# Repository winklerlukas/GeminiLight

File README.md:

GeminiLight
===========

Arduino Temperature MultiColour Project

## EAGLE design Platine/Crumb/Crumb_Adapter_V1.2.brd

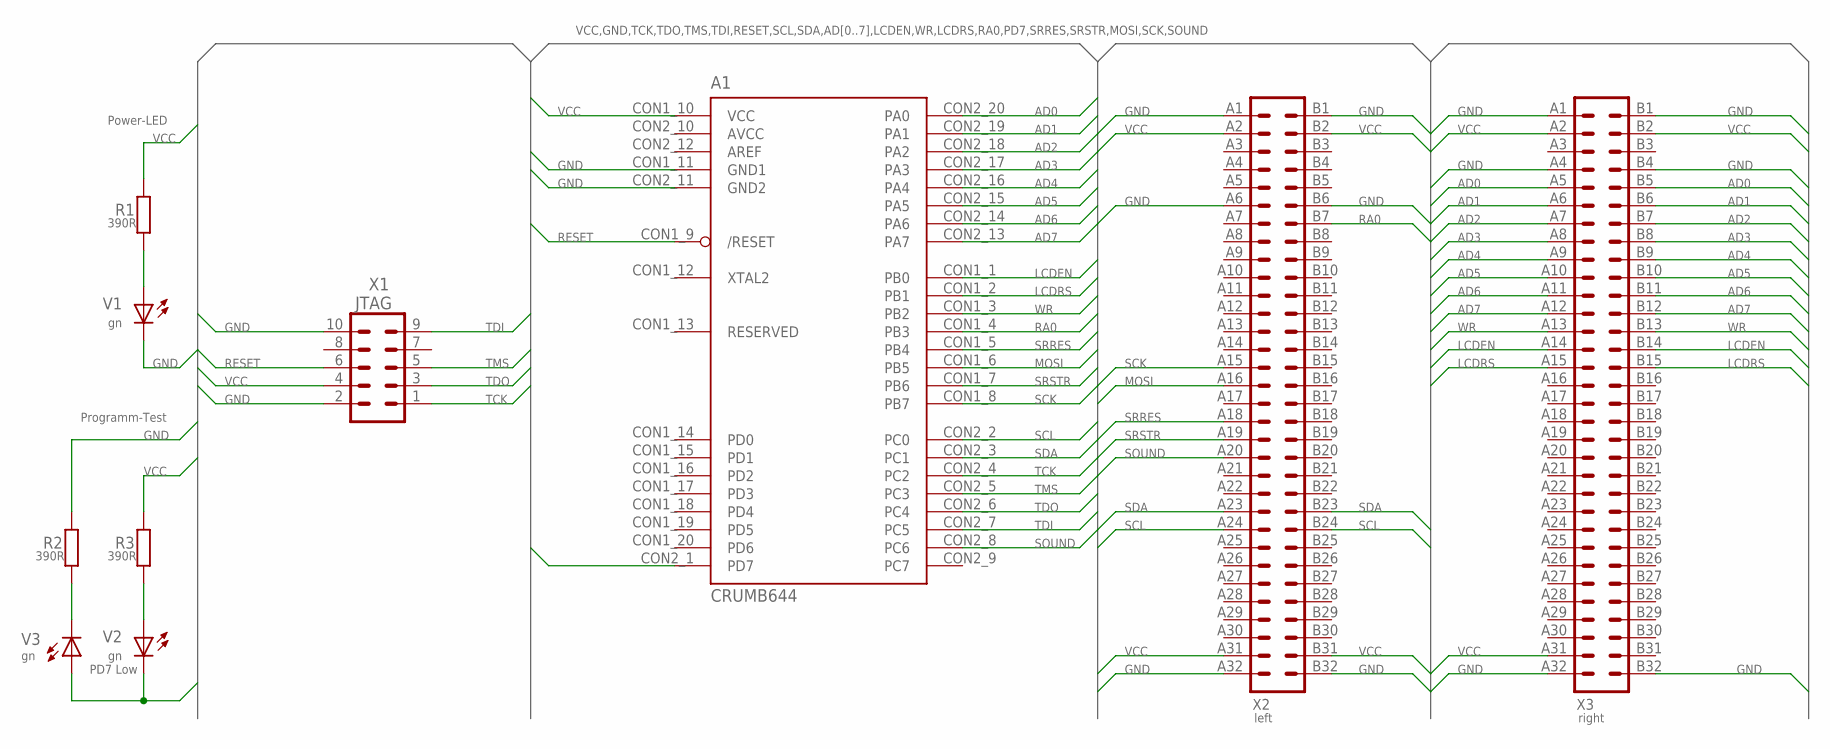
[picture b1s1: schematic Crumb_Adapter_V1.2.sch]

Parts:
A1: CRUMB644
R1, R2, R3: 390R; M1206
V1, V2, V3: gn; CHIPLED_1206
X1: JTAG; MA05-2
X2: left; MAB32-2
X3: right; MAB32-2

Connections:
AD0: A1.CON2_20 (PA0), X3.A5, X3.B5
AD1: A1.CON2_19 (PA1), X3.A6, X3.B6
AD2: A1.CON2_18 (PA2), X3.A7, X3.B7
AD3: A1.CON2_17 (PA3), X3.A8, X3.B8
AD4: A1.CON2_16 (PA4), X3.A9, X3.B9
AD5: A1.CON2_15 (PA5), X3.A10, X3.B10
AD6: A1.CON2_14 (PA6), X3.A11, X3.B11
AD7: A1.CON2_13 (PA7), X3.A12, X3.B12
GND: A1.CON1_11 (GND1), A1.CON2_11 (GND2), R2.2, V1.C, X1.2, X1.10, X2.A1, X2.A6, X2.A32, X2.B1, X2.B6, X2.B32, X3.A1, X3.A4, X3.A32, X3.B1, X3.B4, X3.B32
LCDEN: A1.CON1_1 (PB0), X3.A14, X3.B14
LCDRS: A1.CON1_2 (PB1), X3.A15, X3.B15
MOSI: A1.CON1_6 (PB5), X2.A16
unnamed: R1.1, V1.A
unnamed: R3.1, V2.A
unnamed: R2.1, V3.C
PD7: A1.CON2_1 (PD7), V2.C, V3.A
RA0: A1.CON1_4 (PB3), X2.B7
RESET: A1.CON1_9 (/RESET), X1.6
SCK: A1.CON1_8 (PB7), X2.A15
SCL: A1.CON2_2 (PC0), X2.A24, X2.B24
SDA: A1.CON2_3 (PC1), X2.A23, X2.B23
SOUND: A1.CON2_8 (PC6), X2.A20
SRRES: A1.CON1_5 (PB4), X2.A18
SRSTR: A1.CON1_7 (PB6), X2.A19
TCK: A1.CON2_4 (PC2), X1.1
TDI: A1.CON2_7 (PC5), X1.9
TDO: A1.CON2_6 (PC4), X1.3
TMS: A1.CON2_5 (PC3), X1.5
VCC: A1.CON1_10 (VCC), R1.2, R3.2, X1.4, X2.A2, X2.A31, X2.B2, X2.B31, X3.A2, X3.A31, X3.B2
WR: A1.CON1_3 (PB2), X3.A13, X3.B13

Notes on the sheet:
PD7 Low
Programm-Test
Power-LED

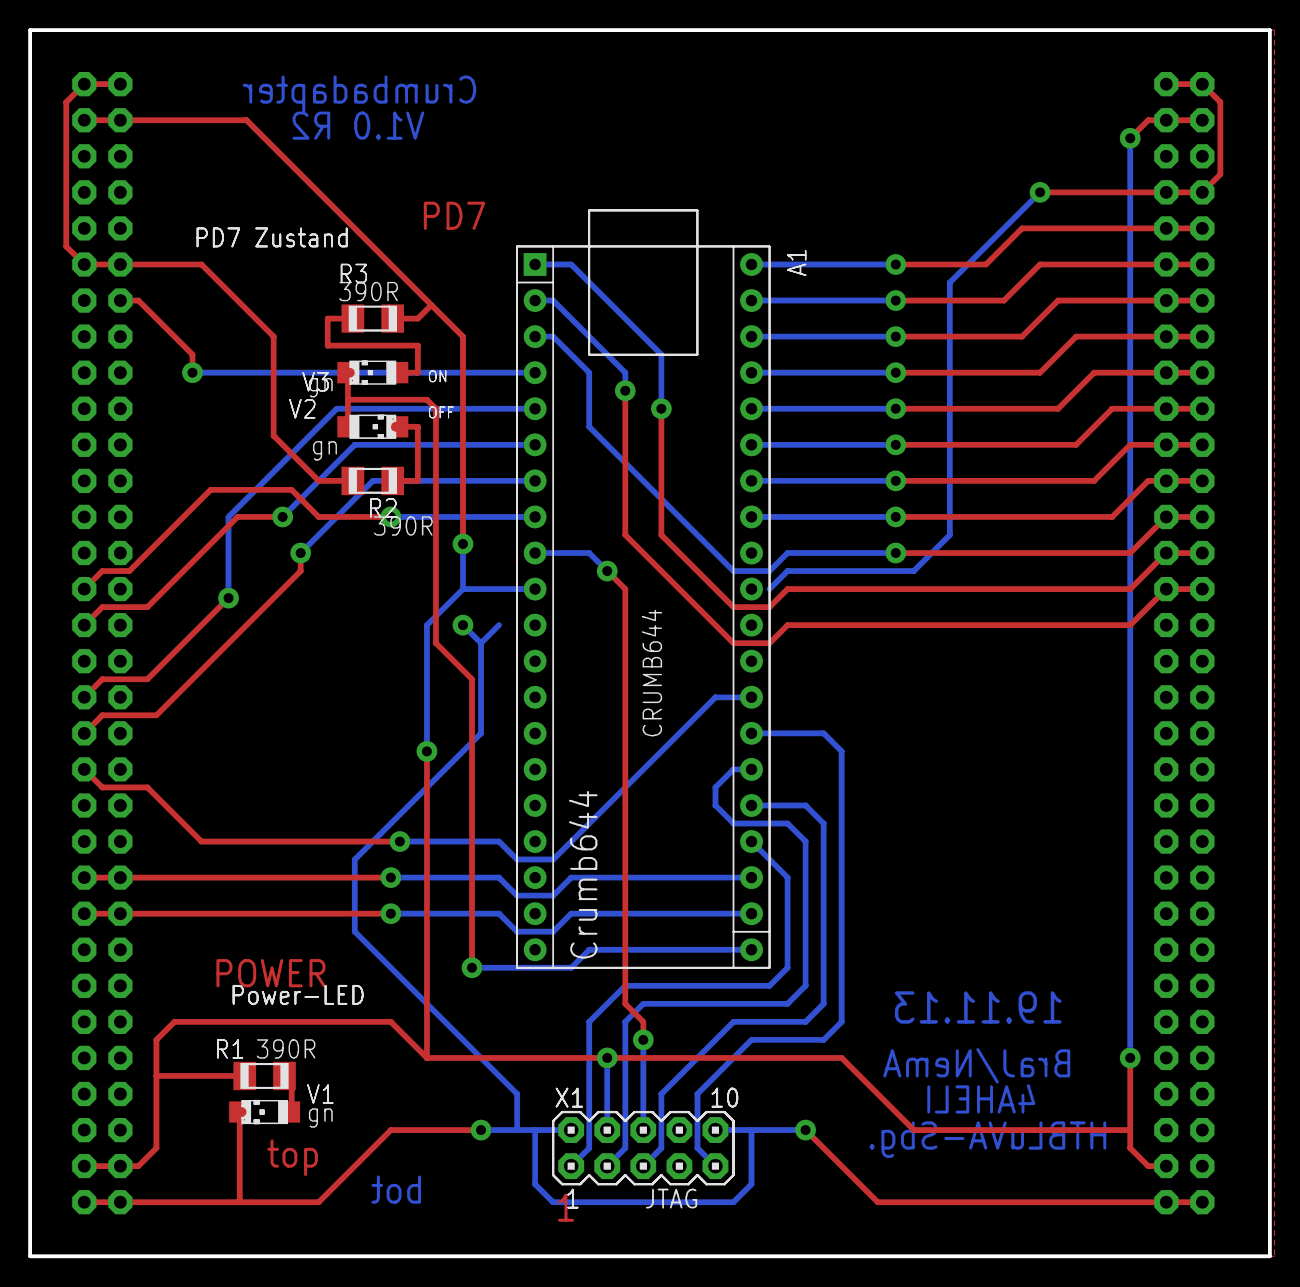
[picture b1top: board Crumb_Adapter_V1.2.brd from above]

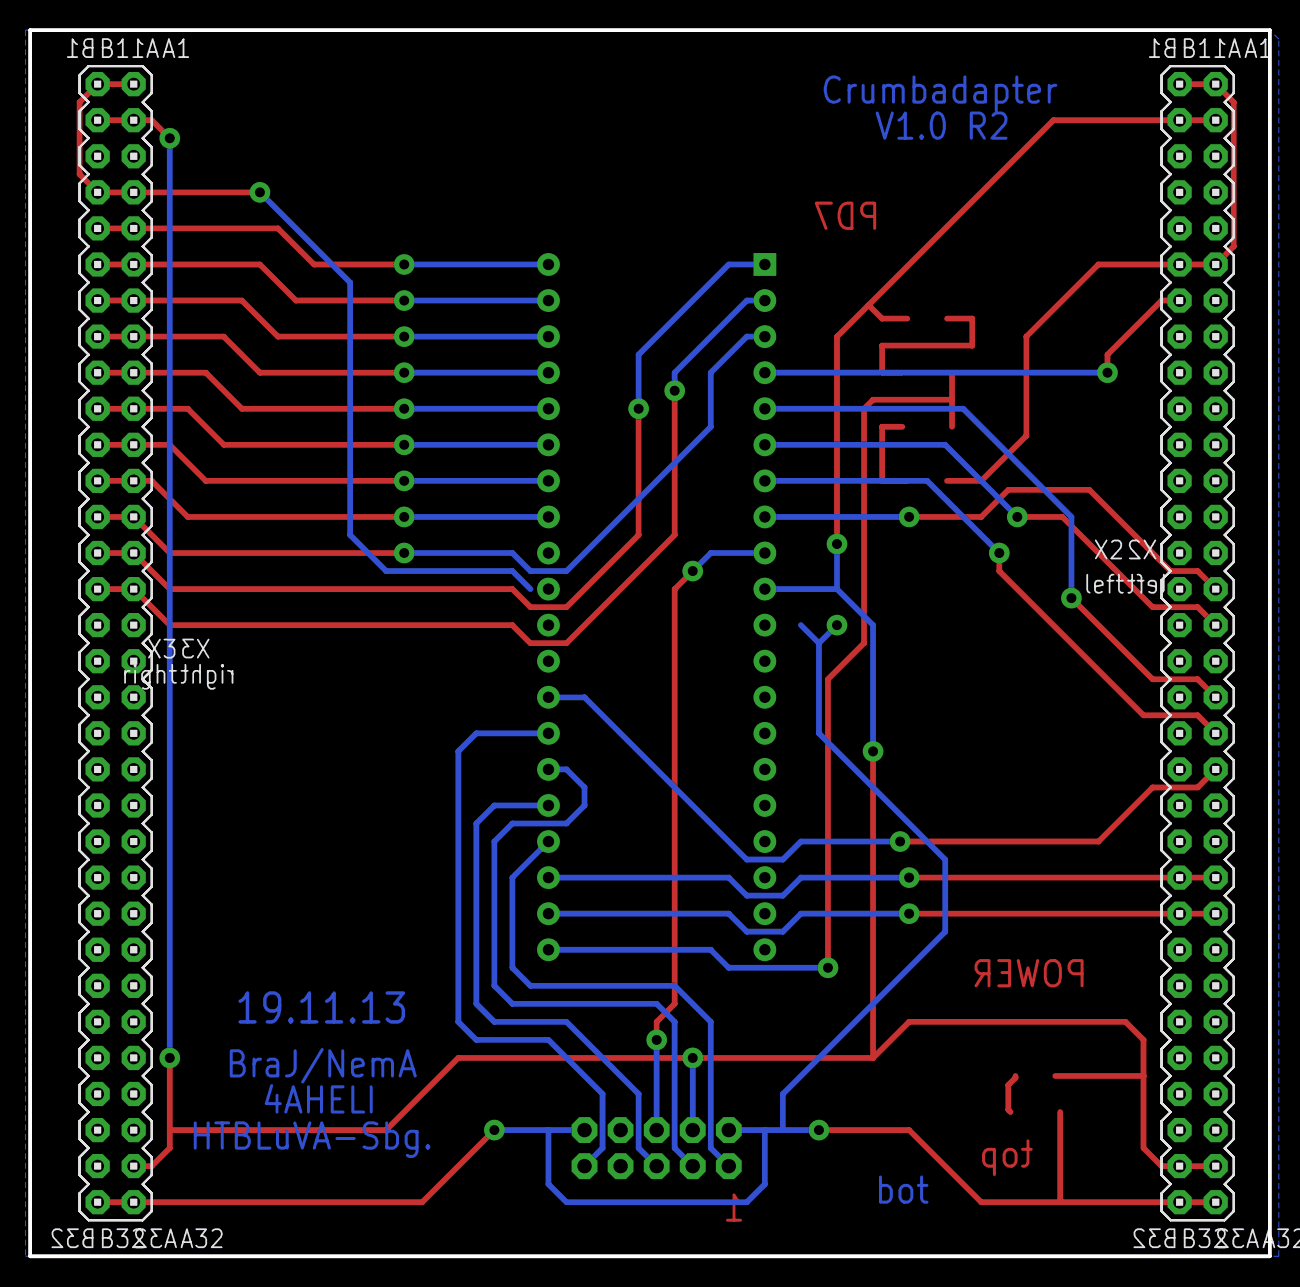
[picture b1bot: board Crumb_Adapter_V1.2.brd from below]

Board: 2 copper layers, 87.3 x 86.3 mm, 12 parts (2 on the bottom side), 30 nets.

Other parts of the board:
DRILEGEND: DRILEGEND
MEASURE: MEASURE

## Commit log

2014-05-28 First Upload
